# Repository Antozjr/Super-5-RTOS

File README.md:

# Gestión electrónica distribuida para un Renault 5 GTL

🇬🇧 [Read this in English](README.en.md)

Sistema electrónico distribuido para un **Renault 5 GTL de 1989** (G-C1J): varios nodos con **FreeRTOS** que se comunican por **bus CAN a 500 kbps**, con firmware en PlatformIO y una PCB combinada (BCM + Gateway) diseñada en KiCad. La idea: modernizar el coche de forma **reversible**, sin modificar el arnés original.

> 🔴 **Desarrollo detenido por una incidencia.** El vehículo sufrió un incendio durante una marcha normal, antes de llegar a instalar el BCM, y el desarrollo se paró ahí. El firmware compilado, el protocolo CAN, la documentación y el diseño de la PCB (Gerbers incluidos) se publican tal cual quedaron, como referencia y como base reutilizable para otro vehículo.

---

## Arquitectura

```mermaid
flowchart LR
    subgraph CAN["Bus CAN · 500 kbps · 11 bit"]
        direction LR
        BCM["BCM<br/>STM32F103C8<br/>carrocería"]
        ICM["ICM<br/>STM32F103C8<br/>instrumentación"]
        UCE["UCE<br/>STM32F405RG<br/>motor (congelada)"]
        GW["Gateway<br/>ESP32 + MCP2515"]
    end
    GW -- "WiFi AP · WebSocket" --> WEB["Navegador<br/>dashboard"]

    style BCM fill:#12161d,stroke:#34d3d1,color:#eef1f5
    style ICM fill:#12161d,stroke:#34d3d1,color:#eef1f5
    style UCE fill:#12161d,stroke:#5f6b7d,color:#9aa4b2,stroke-dasharray: 5 5
    style GW fill:#12161d,stroke:#34d3d1,color:#eef1f5
    style WEB fill:#12161d,stroke:#5f6b7d,color:#eef1f5
```

Cada nodo es una placa independiente con su propio firmware y sus tareas FreeRTOS; todos comparten únicamente el protocolo y los structs de `shared/`.

| Nodo | MCU | Qué hace |
|------|-----|----------|
| **BCM** (Body Control Module) | STM32F103C8 (Blue Pill) | Luces (posición, cruce, antiniebla), bocina y efecto de llamas por relés/MOSFET; lee los mandos por optoacopladores. Modo fail-safe y watchdog. |
| **ICM** (Instrumentation Control Module) | STM32F103C8 (Blue Pill) | Lee RPM (optoacoplador + interrupción), presión de admisión (MPX4250AP), temperatura de refrigerante y de aire (NTC) y tensión de batería (INA219); publica `ENGINE_DATA` cada 50 ms. |
| **UCE** (Engine Control Unit) | STM32F405RG | Gestión de motor (encendido e inyección con tablas, calibración por TunerStudio). Nunca llegó a compilar: congelada. |
| **Gateway** | ESP32 + MCP2515 | Puente CAN ↔ WiFi: reenvía todo el tráfico del bus por WebSocket a un dashboard web servido desde la propia flash (SPIFFS). |

## Funciones destacadas

- **Instalación reversible ("modo transparente").** La PCB intercepta los relés originales del coche, sin tocar el arnés: desconectarla deja el coche de serie. Solo la antiniebla trasera (y, según versión, las luces de posición) tienen relé de fábrica; el resto de canales van en la placa pero se conectan más adelante.
- **Fail-safe CAN.** Si el bus calla más de 5 s, el BCM enciende las luces de posición, hace parpadear el LED de alarma a 5 Hz, bloquea los efectos y, pasados 5 min, apaga las luces para proteger la batería. Vuelve a la normalidad solo cuando detecta actividad.
- **Watchdog.** El IWDG (1 s) solo se alimenta si las tareas críticas (`CAN_RX`, `ALARM`) siguen vivas; si una se bloquea, el nodo se reinicia.
- **Efecto de llamas en el escape.** Patrones definidos como tablas de frames (intensidad + duración) a 30 fps, con activación automática en corte de gas (el ICM detecta RPM altas con MAP bajo y se lo ordena al BCM). Módulo externo desmontable.
- **Dashboard WiFi.** El Gateway crea su propio punto de acceso y sirve una web con los datos del bus en tiempo real.
- **Protocolo compartido y probado.** IDs y estructuras en `shared/`, con tests unitarios nativos (Unity) que no necesitan hardware.

## Protocolo CAN

Tramas estándar de 11 bits a 500 kbps. Cada nodo tiene su rango de IDs:

| Nodo | Rango de IDs |
|------|--------------|
| BCM | `0x100`–`0x1FF` |
| ICM | `0x310`–`0x31F` |
| UCE | `0x400`–`0x41F` |
| Gateway | `0x700` |
| Broadcast (reset) | `0x7FF` |

Todos emiten un *heartbeat* cada segundo con flags de estado y tiempo en marcha. Las tramas, periodos y comandos están en [`docs/CAN.md`](docs/CAN.md) y en [`shared/Protocol.h`](shared/Protocol.h).

## Hardware y PCB

Placa única **BCM + Gateway**, diseñada en KiCad:

- 2 capas, **159,5 × 142,5 mm**, 79 componentes THT más módulos enchufables (Blue Pill, ESP32 DevKit y MCP2515 sobre zócalos, para sustituirlos fácilmente).
- Ruteo automático con Freerouting al 100 %, plano de masa en ambas capas, **DRC sin errores**. Gerbers de las 7 capas y taladros en `Archivos Placa/gerbers/`.
- Un único riel de 5 V (LM2596) para ambos nodos y las bobinas de los relés; un solo par CANH/CANL con terminación de 120 Ω por jumper.
- Protección de entrada de 12 V: fusible de 3 A, MOSFET de protección contra polaridad inversa (IRF9540N) y TVS (P6KE18A).
- Cada relé toma su +12 V del zócalo original interceptado, por lo que se conserva la protección por circuito del propio coche.

La placa **nunca llegó a fabricarse**. El diseño y su justificación están en [`docs/PCB_BCM_GATEWAY.md`](docs/PCB_BCM_GATEWAY.md).

## Estado del proyecto

| Fase | Descripción | Estado |
|------|-------------|--------|
| Fase 1 | Validación del bus CAN en banco (BCM + ICM + Gateway) | ✅ Completada |
| Fase 2 | PCB del BCM + Gateway (KiCad) | ✅ Diseño terminado, Gerbers listos — nunca fabricada |
| Fase 3 | Instalación física en el vehículo | 🔴 No iniciada — desarrollo detenido por el incendio |
| Fase 4 | Gateway completo + UCE (motor) | 🔴 No iniciada |

| Nodo | Firmware | Estado |
|------|----------|--------|
| BCM | v3.2.0 | ✅ Compilado y validado en banco — nunca instalado en el vehículo |
| ICM | v3.1.0 | ✅ Compilado y validado en banco — nunca instalado en el vehículo |
| Gateway | v3.2.0 | ✅ Compilado y validado en banco — nunca instalado en el vehículo |
| UCE | v3.0.0 | ❌ No compila (errores pendientes) — congelada |

## Compilar y probar

Necesitas [PlatformIO](https://platformio.org/) (extensión de VS Code, o `pip install platformio`). Las librerías se descargan solas. Cada nodo es un proyecto independiente:

```bash
cd BCM     && pio run                 # STM32F103 (flasheo con ST-Link: pio run -t upload)
cd ../ICM  && pio run
cd ../Gateway && pio run && pio run -t upload && pio run -t uploadfs   # firmware + dashboard (SPIFFS)
```

Los `platformio.ini` traen puertos serie de mi equipo (`monitor_port`, `upload_port`): ajústalos a los tuyos. Antes de flashear el Gateway, define tu propia contraseña WiFi en `Gateway/src/Config.h` (el valor por defecto es un marcador).

Tests unitarios del protocolo, sin hardware:

```bash
pio test -e test_native --project-dir test/
```

## Estructura del repositorio

```
BCM/  ICM/  UCE/  Gateway/   firmware por nodo (PlatformIO)
shared/                      protocolo y structs CAN comunes
Archivos Placa/              proyecto KiCad y Gerbers de la PCB
Super5.pretty/               librería de footprints propia
test/                        tests unitarios nativos
docs/                        documentación técnica
```

## Documentación

| Documento | Contenido |
|-----------|-----------|
| [`docs/CAN.md`](docs/CAN.md) | Protocolo CAN: IDs, tramas, periodos y modos especiales |
| [`docs/PINOUT.md`](docs/PINOUT.md) | Pinout consolidado de todos los nodos |
| [`docs/BCM_HARDWARE.md`](docs/BCM_HARDWARE.md) | Alimentación, transceptor CAN, relés y optoacopladores del BCM |
| [`docs/PCB_BCM_GATEWAY.md`](docs/PCB_BCM_GATEWAY.md) | Diseño de la placa combinada y notas de fabricación |
| [`docs/BOM.md`](docs/BOM.md) | Lista de materiales |
| [`docs/INSTALL.md`](docs/INSTALL.md) | Compilación, fases de despliegue, instalación por nodo y resolución de problemas |
| [`docs/CHANGELOG.md`](docs/CHANGELOG.md) · [`docs/PROPOSALS.md`](docs/PROPOSALS.md) | Historial de cambios y de decisiones |

## Lecciones aprendidas

- El **TJA1050 necesita 5 V** en VCC (nunca 3,3 V): con 3,3 V el transceptor no transmite y no da ningún error visible.
- En un ST-Link, **SWCLK y SWDIO no son intercambiables**: si falla con `init mode failed`, revisa que no estén cruzados antes de probar otros trucos.

Más detalles en [`docs/INSTALL.md`](docs/INSTALL.md).

## Reutilizar este trabajo

El protocolo CAN, la estructura de nodos y la placa se pueden adaptar a otro vehículo. Si lo haces, ten en cuenta que los mapas de relés y conectores de `docs/` corresponden a un Renault 5 GTL de 1989.

## Licencia

MIT — ver [`LICENSE`](LICENSE).

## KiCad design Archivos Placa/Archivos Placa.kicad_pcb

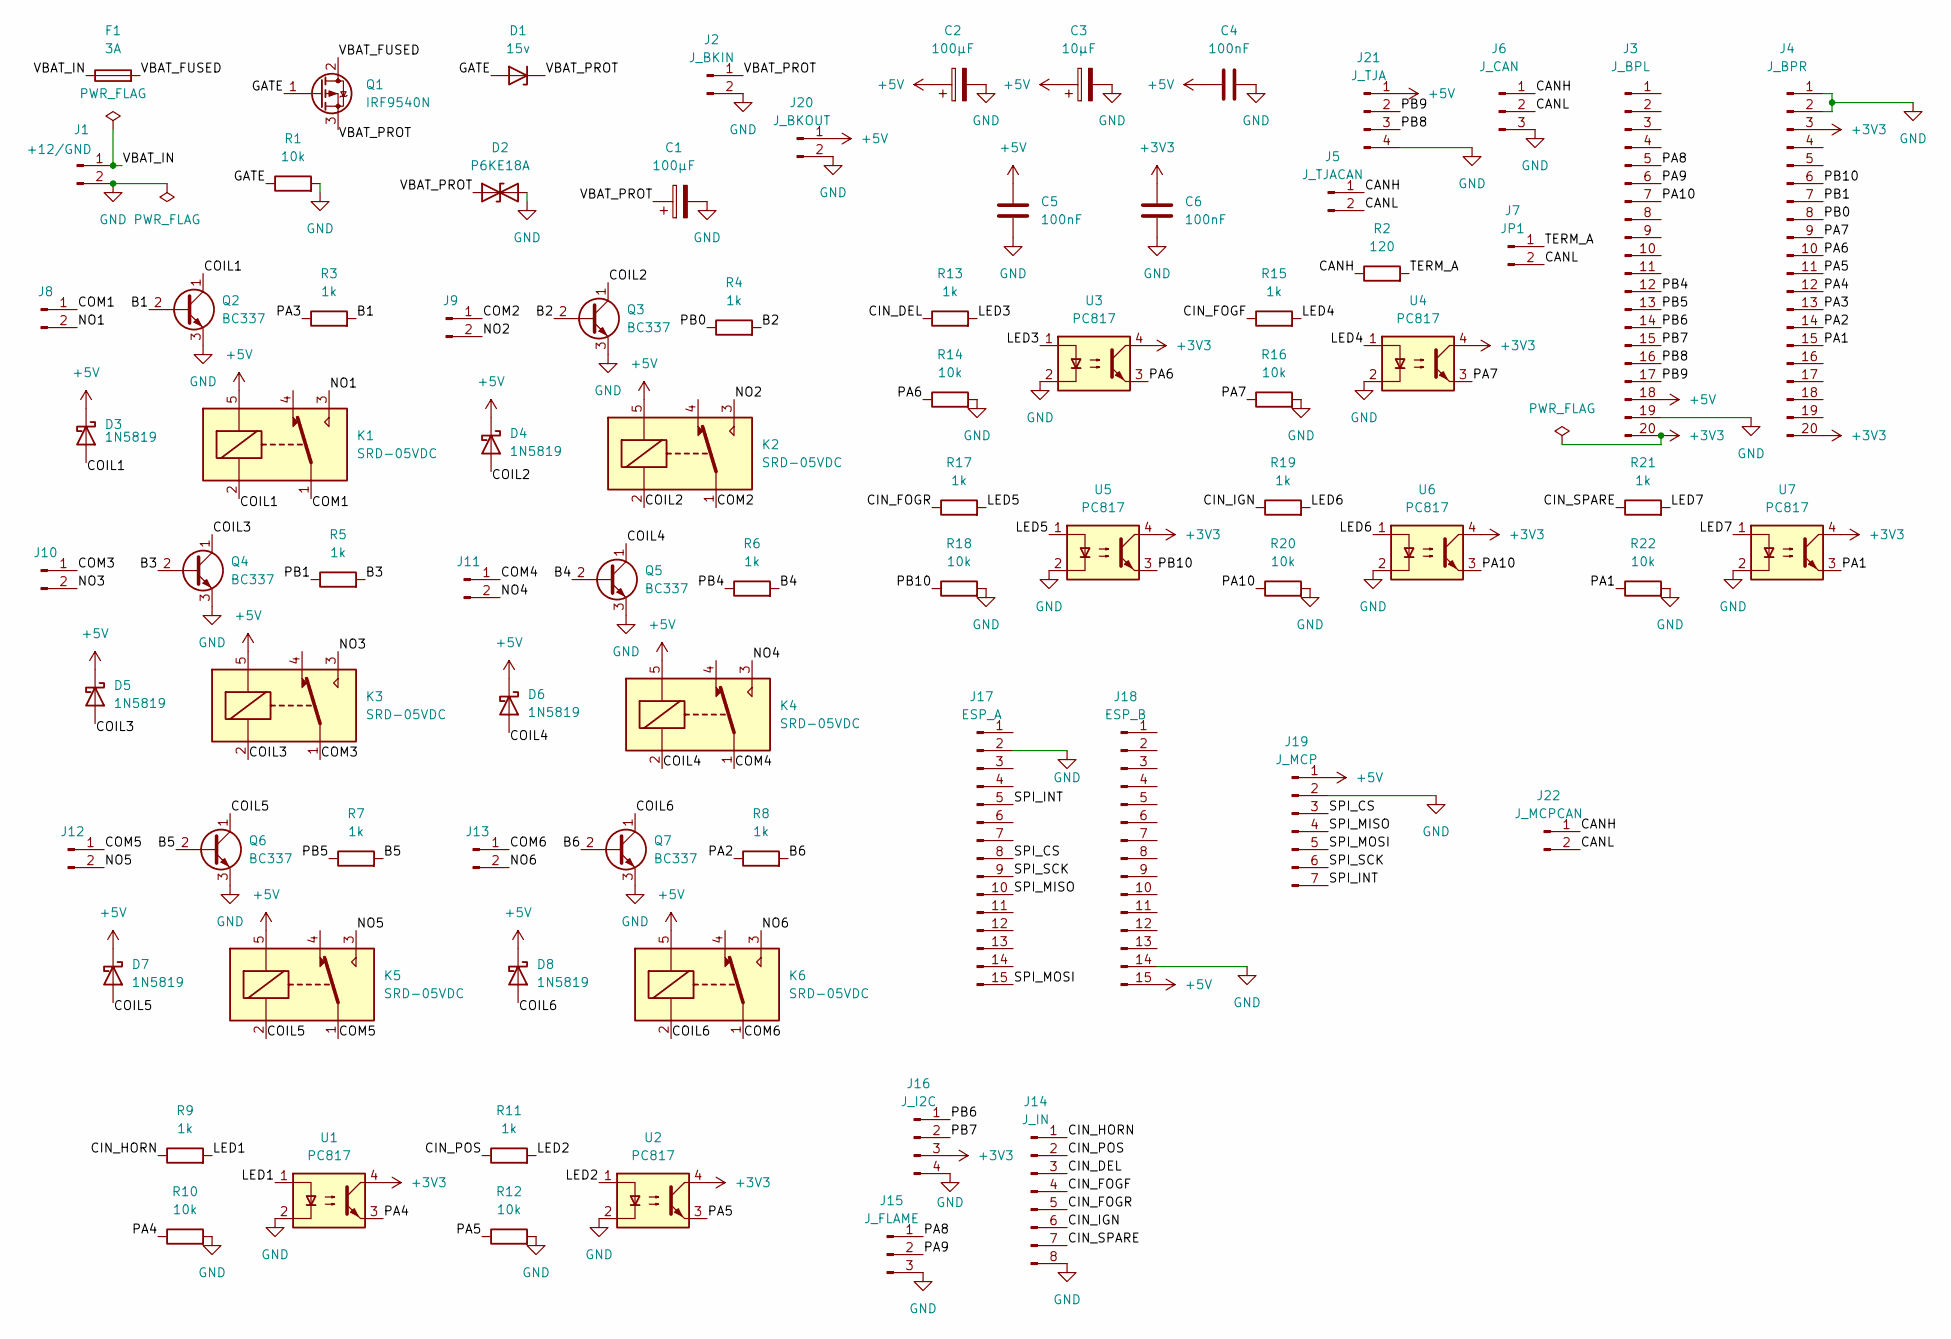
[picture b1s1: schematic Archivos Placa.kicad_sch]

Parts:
C1, C2: 100µF; CP_Radial_D6.3mm_P2.50mm
C3: 10µF; CP_Radial_D6.3mm_P2.50mm
C4, C5, C6: 100nF; C_Disc_D5.0mm_W2.5mm_P5.00mm
D1: 15v; D_DO-35_SOD27_P7.62mm_Horizontal
D2: P6KE18A; D_DO-15_P10.16mm_Horizontal
D3, D4, D5, D6, D7, D8: 1N5819; D_DO-41_SOD81_P10.16mm_Horizontal
F1: 3A; Fuseholder_Blade_Mini_Keystone_3568
J1: +12/GND; TerminalBlock_MaiXu_MX126-5.0-02P_1x02_P5.00mm
J2: J_BKIN; LM2596_pin_pair
J3: J_BPL; PinSocket_1x20_P2.54mm_Vertical
J4: J_BPR; PinSocket_1x20_P2.54mm_Vertical
J5: J_TJACAN; PinHeader_1x02_P2.54mm_Vertical
J6: J_CAN; JST_XH_B3B-XH-A_1x03_P2.50mm_Vertical
J7: JP1; PinHeader_1x02_P2.54mm_Vertical
J8, J9, J10, J11, J12, J13: TerminalBlock_MaiXu_MX126-5.0-02P_1x02_P5.00mm
J14: J_IN; JST_XH_B8B-XH-A_1x08_P2.50mm_Vertical
J15: J_FLAME; JST_XH_B3B-XH-A_1x03_P2.50mm_Vertical
J16: J_I2C; PinHeader_1x04_P2.54mm_Vertical
J17: ESP_A; PinSocket_1x15_P2.54mm_Vertical
J18: ESP_B; PinSocket_1x15_P2.54mm_Vertical
J19: J_MCP; PinSocket_1x07_P2.54mm_Vertical
J20: J_BKOUT; LM2596_pin_pair
J21: J_TJA; PinSocket_1x04_P2.54mm_Vertical
J22: J_MCPCAN; PinHeader_1x02_P2.54mm_Vertical
K1, K2, K3, K4, K5, K6: SRD-05VDC; Relay_SPDT_SANYOU_SRD_Series_Form_C
Q1: IRF9540N; TO-220-3_Vertical
Q2, Q3, Q4, Q5, Q6, Q7: BC337; TO-92_Inline
R1, R10, R12, R14, R16, R18, R20, R22: 10k; R_Axial_DIN0207_L6.3mm_D2.5mm_P10.16mm_Horizontal
R2: 120; R_Axial_DIN0207_L6.3mm_D2.5mm_P10.16mm_Horizontal
R3, R4, R5, R6, R7, R8, R9, R11, R13, R15, R17, R19, R21: 1k; R_Axial_DIN0207_L6.3mm_D2.5mm_P10.16mm_Horizontal
U1, U2, U3, U4, U5, U6, U7: PC817; DIP-4_W7.62mm

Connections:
+3V3: C6.1, J3.20, J4.3, J4.20, J16.3, U1.4, U2.4, U3.4, U4.4, U5.4, U6.4, U7.4
+5V: C2.1, C3.1, C4.2, C5.1, D3.1 (K), D4.1 (K), D5.1 (K), D6.1 (K), D7.1 (K), D8.1 (K), J3.18, J18.15, J19.1, J20.1, J21.1, K1.5, K2.5, K3.5, K4.5, K5.5, K6.5
/B1: Q2.2 (B), R3.2
/B2: Q3.2 (B), R4.2
/B3: Q4.2 (B), R5.2
/B4: Q5.2 (B), R6.2
/B5: Q6.2 (B), R7.2
/B6: Q7.2 (B), R8.2
/CANH: J5.1, J6.1, J22.1, R2.1
/CANL: J5.2, J6.2, J7.2, J22.2
/CIN_DEL: J14.3, R13.1
/CIN_FOGF: J14.4, R15.1
/CIN_FOGR: J14.5, R17.1
/CIN_HORN: J14.1, R9.1
/CIN_IGN: J14.6, R19.1
/CIN_POS: J14.2, R11.1
/CIN_SPARE: J14.7, R21.1
/COIL1: D3.2 (A), K1.2, Q2.1 (C)
/COIL2: D4.2 (A), K2.2, Q3.1 (C)
/COIL3: D5.2 (A), K3.2, Q4.1 (C)
/COIL4: D6.2 (A), K4.2, Q5.1 (C)
/COIL5: D7.2 (A), K5.2, Q6.1 (C)
/COIL6: D8.2 (A), K6.2, Q7.1 (C)
/COM1: J8.1, K1.1
/COM2: J9.1, K2.1
/COM3: J10.1, K3.1
/COM4: J11.1, K4.1
/COM5: J12.1, K5.1
/COM6: J13.1, K6.1
/GATE: D1.2 (A), Q1.1 (G), R1.1
/LED1: R9.2, U1.1
/LED2: R11.2, U2.1
/LED3: R13.2, U3.1
/LED4: R15.2, U4.1
/LED5: R17.2, U5.1
/LED6: R19.2, U6.1
/LED7: R21.2, U7.1
/NO1: J8.2, K1.3
/NO2: J9.2, K2.3
/NO3: J10.2, K3.3
/NO4: J11.2, K4.3
/NO5: J12.2, K5.3
/NO6: J13.2, K6.3
/PA1: J4.15, R22.1, U7.3
/PA2: J4.14, R8.1
/PA3: J4.13, R3.1
/PA4: J4.12, R10.1, U1.3
/PA5: J4.11, R12.1, U2.3
/PA6: J4.10, R14.1, U3.3
/PA7: J4.9, R16.1, U4.3
/PA8: J3.5, J15.1
/PA9: J3.6, J15.2
/PA10: J3.7, R20.1, U6.3
/PB0: J4.8, R4.1
/PB1: J4.7, R5.1
/PB4: J3.12, R6.1
/PB5: J3.13, R7.1
/PB6: J3.14, J16.1
/PB7: J3.15, J16.2
/PB8: J3.16, J21.3
/PB9: J3.17, J21.2
/PB10: J4.6, R18.1, U5.3
/SPI_CS: J17.8, J19.3
/SPI_INT: J17.5, J19.7
/SPI_MISO: J17.10, J19.4
/SPI_MOSI: J17.15, J19.5
/SPI_SCK: J17.9, J19.6
/TERM_A: J7.1, R2.2
/VBAT_FUSED: F1.2, Q1.2 (D)
/VBAT_IN: F1.1, J1.1
/VBAT_PROT: C1.1, D1.1 (K), D2.1 (A1), J2.1, Q1.3 (S)
GND: C1.2, C2.2, C3.2, C4.1, C5.2, C6.2, D2.2 (A2), J1.2, J2.2, J3.19, J4.1, J4.2, J6.3, J14.8, J15.3, J16.4, J17.2, J18.14, J19.2, J20.2, J21.4, Q2.3 (E), Q3.3 (E), Q4.3 (E), Q5.3 (E), Q6.3 (E), Q7.3 (E), R1.2, R10.2, R12.2, R14.2, R16.2, R18.2, R20.2, R22.2, U1.2, U2.2, U3.2, U4.2, U5.2, U6.2, U7.2

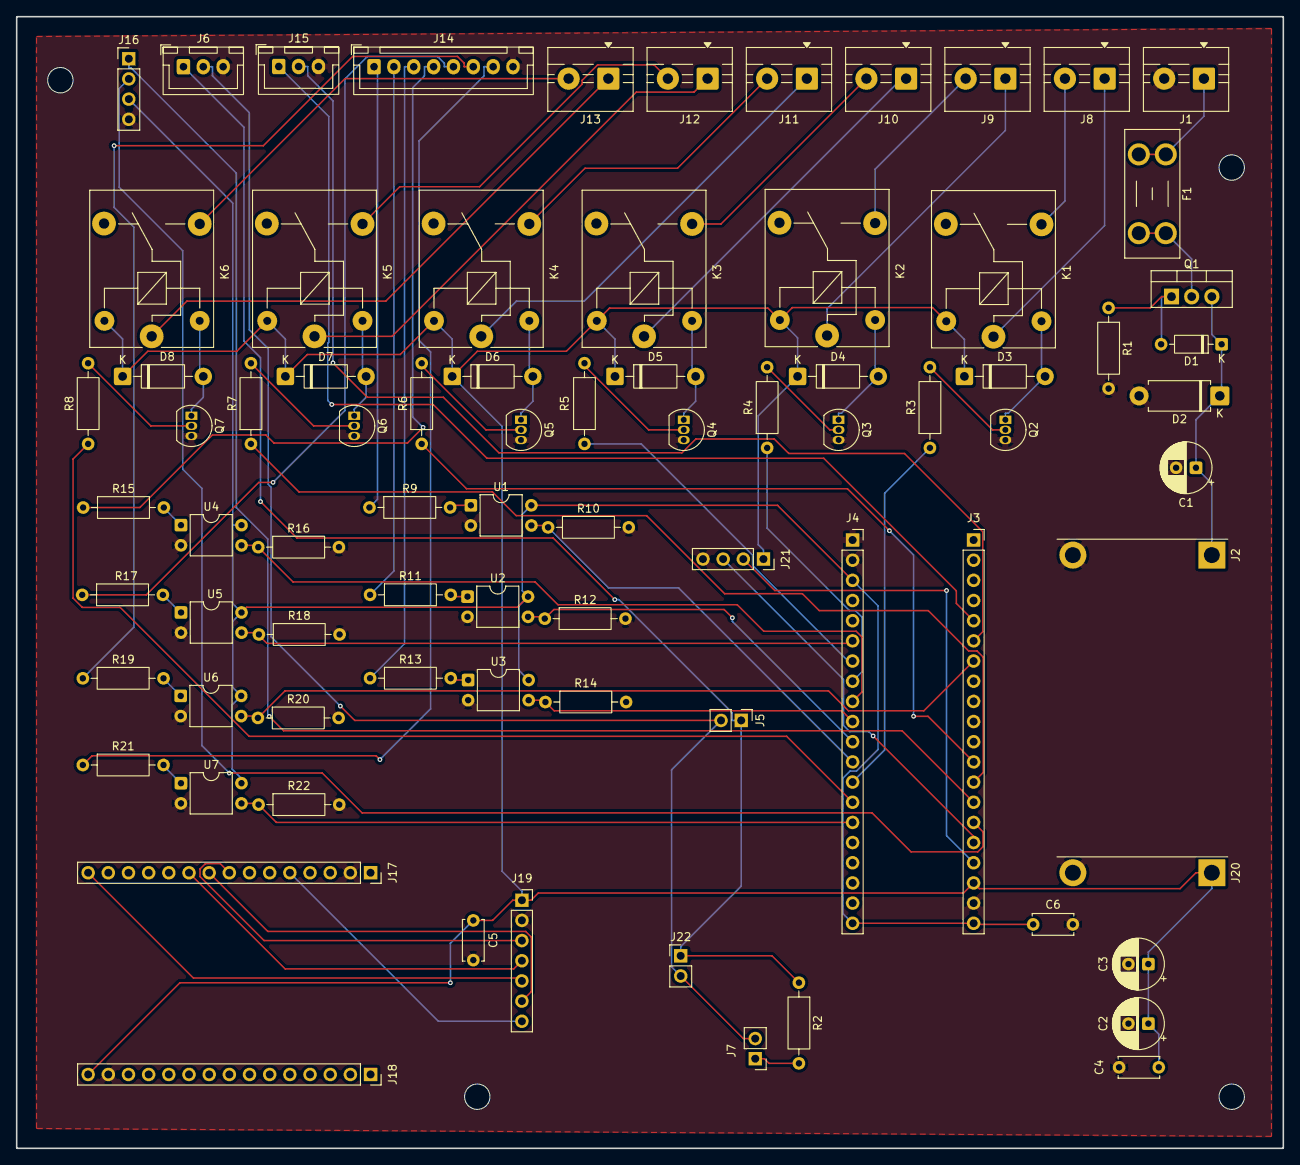
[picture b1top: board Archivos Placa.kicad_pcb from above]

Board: 2 copper layers, 159.5 x 142.5 mm, 83 parts (0 on the bottom side), 72 nets.

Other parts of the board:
H1, H2, H3, H4: MountingHole_3.2mm_M3

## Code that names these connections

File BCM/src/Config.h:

#ifndef CONFIG_H
#define CONFIG_H

/**
 * Config.h - BCM (Body Control Module)
 * STM32F103C8 @ 72MHz
 *
 * Centraliza todos los pines y constantes del nodo BCM.
 * Modificar aquí antes de compilar si el hardware cambia.
 */

// =============================================================================
// HARDWARE PINS
// =============================================================================

// LED de estado (activo en bajo en Blue Pill)
#define PIN_LED_STATUS      PC13

// CAN Bus (STM32F103 CAN remapeado a PB8/PB9)
#define PIN_CAN_RX          PB8
#define PIN_CAN_TX          PB9

// Bocina
#define PIN_HORN_OUT        PA3     // Salida relé bocina (Sec87 pos.9)

// Luces — salidas relé
#define PIN_LIGHT_POS       PB0     // Luces posición     (Sec87 pos.6)
#define PIN_LIGHT_DEL       PB1     // Luces delanteras   (Sec87 pos.10 — cruce/largas via palanca)
#define PIN_LIGHT_FOG_F     PB4     // Antiniebla del.    (Sec87 pos.8)
#define PIN_LIGHT_FOG_R     PB5     // Antiniebla tras.   (Sec81 conector dorado vía 6)

// Entradas mando — 12V coche → PC817 → STM32 (pulldown 10kΩ externo)
#define PIN_IN_HORN         PA4     // Botón bocina stalk (pin86 zócalo pos.9)
#define PIN_IN_LIGHT_POS    PA5     // Mando luces posición (pin86 zócalo pos.6)
#define PIN_IN_LIGHT_DEL    PA6     // Mando luces delanteras (pin86 zócalo pos.10)
#define PIN_IN_FOG_F        PA7     // Interruptor antiniebla del. (pin86 zócalo pos.8)
#define PIN_IN_FOG_R        PB10    // Interruptor antiniebla tras.

// Flames (salida PWM o digital hacia controlador pirotécnico)
#define PIN_FLAME_OUT       PA8     // Salida principal flames (Timer1 CH1)
#define PIN_FLAME_TRIGGER   PA9     // Trigger disparo

// EEPROM (I2C AT24C32 o similar)
#define PIN_I2C_SDA         PB6
#define PIN_I2C_SCL         PB7

// =============================================================================
// CAN PROTOCOL
// =============================================================================
#define CAN_SPEED           500000  // 500 kbps
#define CAN_NODE_ID         0x01    // ID del nodo BCM

// Filtros CAN: aceptar comandos hacia BCM
#define CAN_FILTER_ID       0x180   // Base comandos BCM
#define CAN_FILTER_MASK     0x780   // Aceptar 0x180-0x18F y 0x7FF (broadcast)

// =============================================================================
// TIMING TAREAS (ms)
// =============================================================================
#define TASK_HEARTBEAT_MS   1000
#define TASK_CAN_TX_MS      50
#define TASK_CAN_RX_MS      10
#define TASK_MONITOR_MS     20
#define TASK_HORN_MS        20
#define TASK_FLAMES_MS      33     // ~30 fps animación flames

// =============================================================================
// STACK SIZES (palabras de 32 bits)
// =============================================================================
#define STACK_HEARTBEAT     128
#define STACK_CAN_TX        256
#define STACK_CAN_RX        256
#define STACK_MONITOR       256
#define STACK_HORN          128
#define STACK_FLAMES        512

// =============================================================================
// PRIORIDADES TAREAS (mayor número = mayor prioridad)
// =============================================================================
#define PRIO_HEARTBEAT      1
#define PRIO_MONITOR        3
#define PRIO_HORN           3
#define PRIO_FLAMES         2
#define PRIO_CAN_TX         2
#define PRIO_CAN_RX         4   // Máxima: respuesta rápida al bus CAN

// =============================================================================
// FLAMES - Configuración
// =============================================================================
#define FLAME_PATTERNS      13   // Número de patrones disponibles
#define FLAME_MAX_SPEED     255
#define FLAME_DEFAULT_PATTERN 0

// =============================================================================
// WATCHDOG (IWDG) — PRO-001
// =============================================================================
#define IWDG_TIMEOUT_MS         1000    // 1s — margen suficiente durante boot

// Flags de las tareas críticas que deben estar vivas para kik ear el IWDG
#define WDG_FLAG_CAN_RX         (1 << 0)
#define WDG_FLAG_MONITOR        (1 << 1)
#define WDG_FLAGS_ALL           (WDG_FLAG_CAN_RX | WDG_FLAG_MONITOR)

// =============================================================================
// FAIL-SAFE CAN — PRO-002
// =============================================================================
#define FAILSAFE_CAN_TIMEOUT_MS      5000UL           // 5s sin CAN → modo seguro
#define FAILSAFE_LIGHTS_TIMEOUT_MS   (5UL*60UL*1000UL) // 5min en fail-safe → apagar luces

// =============================================================================
// BOCINA
// =============================================================================
#define HORN_QUEUE_LEN          4       // Comandos on/off en la cola FreeRTOS

// =============================================================================
// STACK WATCHDOG
// =============================================================================
#define STACK_WATCHDOG          128
#define PRIO_WATCHDOG           1       // Baja — solo corre cuando los críticos descansan

// =============================================================================
// POWER MANAGEMENT — PRO-011
// =============================================================================
#define PIN_IGN_SENSE           PA10    // HIGH = +15 presente; LOW = contacto off
#define IGN_OFF_DEBOUNCE_MS     1000UL  // PA10 LOW estable 1s → apagar salidas y entrar en reposo
#define STACK_POWER_MGR         128
#define PRIO_POWER_MGR          2

// =============================================================================
// VERSION
// =============================================================================
#ifndef FIRMWARE_VERSION
#define FIRMWARE_VERSION    "3.3.0"
#endif
#define NODE_NAME           "BCM"

#endif // CONFIG_H

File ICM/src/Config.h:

#ifndef CONFIG_H
#define CONFIG_H

/**
 * Config.h - ICM (Instrumentation Control Module)
 * STM32F103C8 @ 72MHz
 *
 * Sensores: RPM, MAP, CLT, IAT, Batería
 */

// =============================================================================
// HARDWARE PINS
// =============================================================================

#define PIN_LED_STATUS      PC13

// CAN Bus
#define PIN_CAN_RX          PB8
#define PIN_CAN_TX          PB9

// RPM (optoacoplador PC817 en entrada digital con interrupción)
#define PIN_RPM_INPUT       PA0     // Interrupción externa EXTI0

// Sensores ADC (PA1-PA3 → ADC1 canales 1-3)
#define PIN_ADC_MAP         PA1     // MPX4250AP → presión múltiple
#define PIN_ADC_CLT         PA2     // NTC 10K   → temperatura refrigerante
#define PIN_ADC_IAT         PA3     // NTC 10K   → temperatura aire
// PA4 libre (antes divisor batería, sustituido por INA219 vía I2C)

// INA219 — tensión batería vía I2C
// SDA = PB6 (I2C1), SCL = PB7 (I2C1) — pines por defecto Wire en STM32F103
#define INA219_I2C_ADDR     0x40    // ADDR pin a GND (dirección por defecto)

// Poner a 1 cuando el módulo INA219 esté físicamente conectado.
// Con 0: Wire no se inicializa y batt_mv queda a 0 (evita HardFault sin hardware).
#define INA219_ENABLED      0

// =============================================================================
// ADC - CALIBRACIÓN SENSORES
// =============================================================================

// ADC referencia
#define ADC_VREF_MV         3300    // mV
#define ADC_COUNTS          4096    // 12 bits (usar este, no ADC_RESOLUTION que conflicta con Arduino.h)

// Media móvil (PRO-003): número de muestras por canal MAP/CLT/IAT
#define SENSORS_AVG_SAMPLES 8

// MAP - MPX4250AP: Vout = Vcc × (0.00369 × kPa - 0.04)
// Rango: 20kPa (0.25V) → 250kPa (4.75V)
#define MAP_VOUT_MIN_MV     250
#define MAP_VOUT_MAX_MV     4750
#define MAP_KPA_MIN         20
#define MAP_KPA_MAX         250

// CLT / IAT - NTC 10K (divisor con R_pull = 10K)
// Usar tabla Steinhart-Hart o lookup table
#define NTC_RPULL_OHM       10000
#define NTC_BETA            3950
#define NTC_R0_OHM          10000
#define NTC_T0_K            298     // 25°C en Kelvin

// INA219 — rangos de calibración
// Batería coche: 10.5V (descargada) – 14.8V (alternador)
// Usar calibración 32V/2A: bus voltage range 26V HW, resolución 1.6mV
#define INA219_CAL_MAX_V    32      // setCalibration_32V_2A()
#define INA219_BATT_MIN_MV  8000    // Por debajo: batería muy descargada → error
#define INA219_BATT_MAX_MV  16000   // Por encima: fallo regulador → error

// =============================================================================
// RPM - Cálculo
// =============================================================================

// Número de pulsos por revolución del distribuidor (Renault 5 GTL)
#define RPM_PULSES_PER_REV  2       // 4 cilindros / 2 = 2 pulsos por vuelta
#define RPM_TIMEOUT_MS      500     // Sin pulso = 0 RPM

// =============================================================================
// CAN PROTOCOL
// =============================================================================

#define CAN_SPEED           500000
#define CAN_NODE_ID         0x03

// =============================================================================
// IWDG (PRO-009.1)
// =============================================================================

#define IWDG_TIMEOUT_MS         1000
#define WDG_FLAG_SENSORS        (1 << 0)
#define WDG_FLAG_CAN_RX         (1 << 1)
#define WDG_FLAGS_ALL           (WDG_FLAG_SENSORS | WDG_FLAG_CAN_RX)

// =============================================================================
// TIMING TAREAS (ms)
// =============================================================================

#define TASK_HEARTBEAT_MS   1000
#define TASK_SENSORS_MS     50      // 20 Hz lectura sensores
#define TASK_RPM_MS         10      // 100 Hz cálculo RPM
#define TASK_CAN_TX_MS      50      // 20 Hz transmisión
#define TASK_CAN_RX_MS      10
#define TASK_DIAG_MS        500

// =============================================================================
// STACK SIZES
// Reducidos respecto al BCM: Wire + INA219 consumen RAM estática adicional
// en el ICM, dejando menos heap disponible para FreeRTOS.
// =============================================================================

#define STACK_HEARTBEAT     80
#define STACK_SENSORS       192
#define STACK_RPM           80
#define STACK_CAN_TX        128
#define STACK_CAN_RX        128
#define STACK_WATCHDOG      80
#define STACK_DIAG          80

// =============================================================================
// PRIORIDADES
// =============================================================================

#define PRIO_HEARTBEAT      1
#define PRIO_SENSORS        2
#define PRIO_RPM            3       // Alta: tiempo real
#define PRIO_CAN_TX         2
#define PRIO_CAN_RX         4
#define PRIO_WATCHDOG       1
#define PRIO_DIAG           1

// =============================================================================
// VERSION
// =============================================================================

#ifndef FIRMWARE_VERSION
#define FIRMWARE_VERSION    "3.1.0"
#endif
#define NODE_NAME           "ICM"

#endif // CONFIG_H

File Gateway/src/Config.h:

#ifndef CONFIG_H
#define CONFIG_H

/**
 * Config.h - Gateway (WiFi ↔ CAN Bridge)
 * ESP32 @ 240MHz dual-core
 *
 * Core 0: CAN RX/TX (tiempo real)
 * Core 1: HTTP/WebSocket (servidor web)
 */

// =============================================================================
// HARDWARE PINS (MCP2515 SPI)
// =============================================================================

// MCP2515 CAN Controller via SPI
#define PIN_SPI_SCK         18
#define PIN_SPI_MISO        19
#define PIN_SPI_MOSI        23
#define PIN_MCP2515_CS      5
#define PIN_MCP2515_INT     4   // Interrupción MCP2515

// LED de estado
#define PIN_LED_STATUS      2   // LED integrado ESP32

// =============================================================================
// WIFI
// =============================================================================

#define WIFI_SSID           "CHANGE_ME"
#define WIFI_PASSWORD       "CHANGE_ME_MIN_8_CHARS"   // No usar el valor por defecto — definir localmente antes de flashear
#define WIFI_IP             "192.168.4.1"
#define WIFI_GATEWAY        "192.168.4.1"
#define WIFI_SUBNET         "255.255.255.0"

// =============================================================================
// SERVIDORES
// =============================================================================

#define HTTP_PORT           80
#define WS_PORT             81

// REST API endpoints
#define API_BASE            "/api/v1"
#define API_STATUS          "/api/v1/status"
#define API_ENGINE          "/api/v1/engine"
#define API_BCM             "/api/v1/bcm"
#define API_COMMAND         "/api/v1/command"

// =============================================================================
// CAN
// =============================================================================

#define CAN_BUS_SPEED       500000   // 500 kbps
#define CAN_QUEUE_SIZE      32       // Mensajes en cola RX/TX

// =============================================================================
// WEBSOCKET
// =============================================================================

#define WS_BROADCAST_MS     100      // Intervalo broadcast a clientes (ms)
#define WS_MAX_CLIENTS      4

// =============================================================================
// TIMING TAREAS
// =============================================================================

#define TASK_CAN_RX_MS      5
#define TASK_CAN_TX_MS      20
#define TASK_WS_BCAST_MS    100
#define TASK_HEARTBEAT_MS   1000

// =============================================================================
// POWER MANAGEMENT
// =============================================================================

// Tiempo sin tráfico CAN antes de entrar en deep sleep (ms).
// Con heartbeats a 1 Hz, equivale a 30 latidos perdidos consecutivos.
// Funciona en conjunción con PRO-011 (BCM STOP mode): cuando BCM/ICM
// dejan de transmitir al apagarse el contacto, este timeout se dispara.
#define POWER_SLEEP_TIMEOUT_MS  30000

// =============================================================================
// VERSION
// =============================================================================

#ifndef FIRMWARE_VERSION
#define FIRMWARE_VERSION    "3.2.0"
#endif
#define NODE_NAME           "Gateway"

#endif // CONFIG_H
